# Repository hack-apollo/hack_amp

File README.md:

HACK LABS POWER AMP (TPA3116D2) : https://www.youtube.com/watch?v=O-adCBWkxsg&t=2s                                                                             
Author: HACK实验室                                                                                     
YouTube ID: HACK实验室, welcome to subscribe https://www.youtube.com/c/HACK实验室                                                       
HACK_PowerAmp is a free download and may be used, modified, evaluated and
distributed without charge provided the user adheres to version three of the GNU
General Public License (GPL) and does not remove the copyright notice or this
text.  The GPL V3 text is available on the gnu.org web site
作者：HACK实验室                                                                                        
B站ID：HACK实验室  欢迎订阅 https://space.bilibili.com/395145107                                                                            
微信公众号：HACK实验室，开源资料唯一发布点，定期分享开源硬件以及有价值的技术文章，欢迎关注.

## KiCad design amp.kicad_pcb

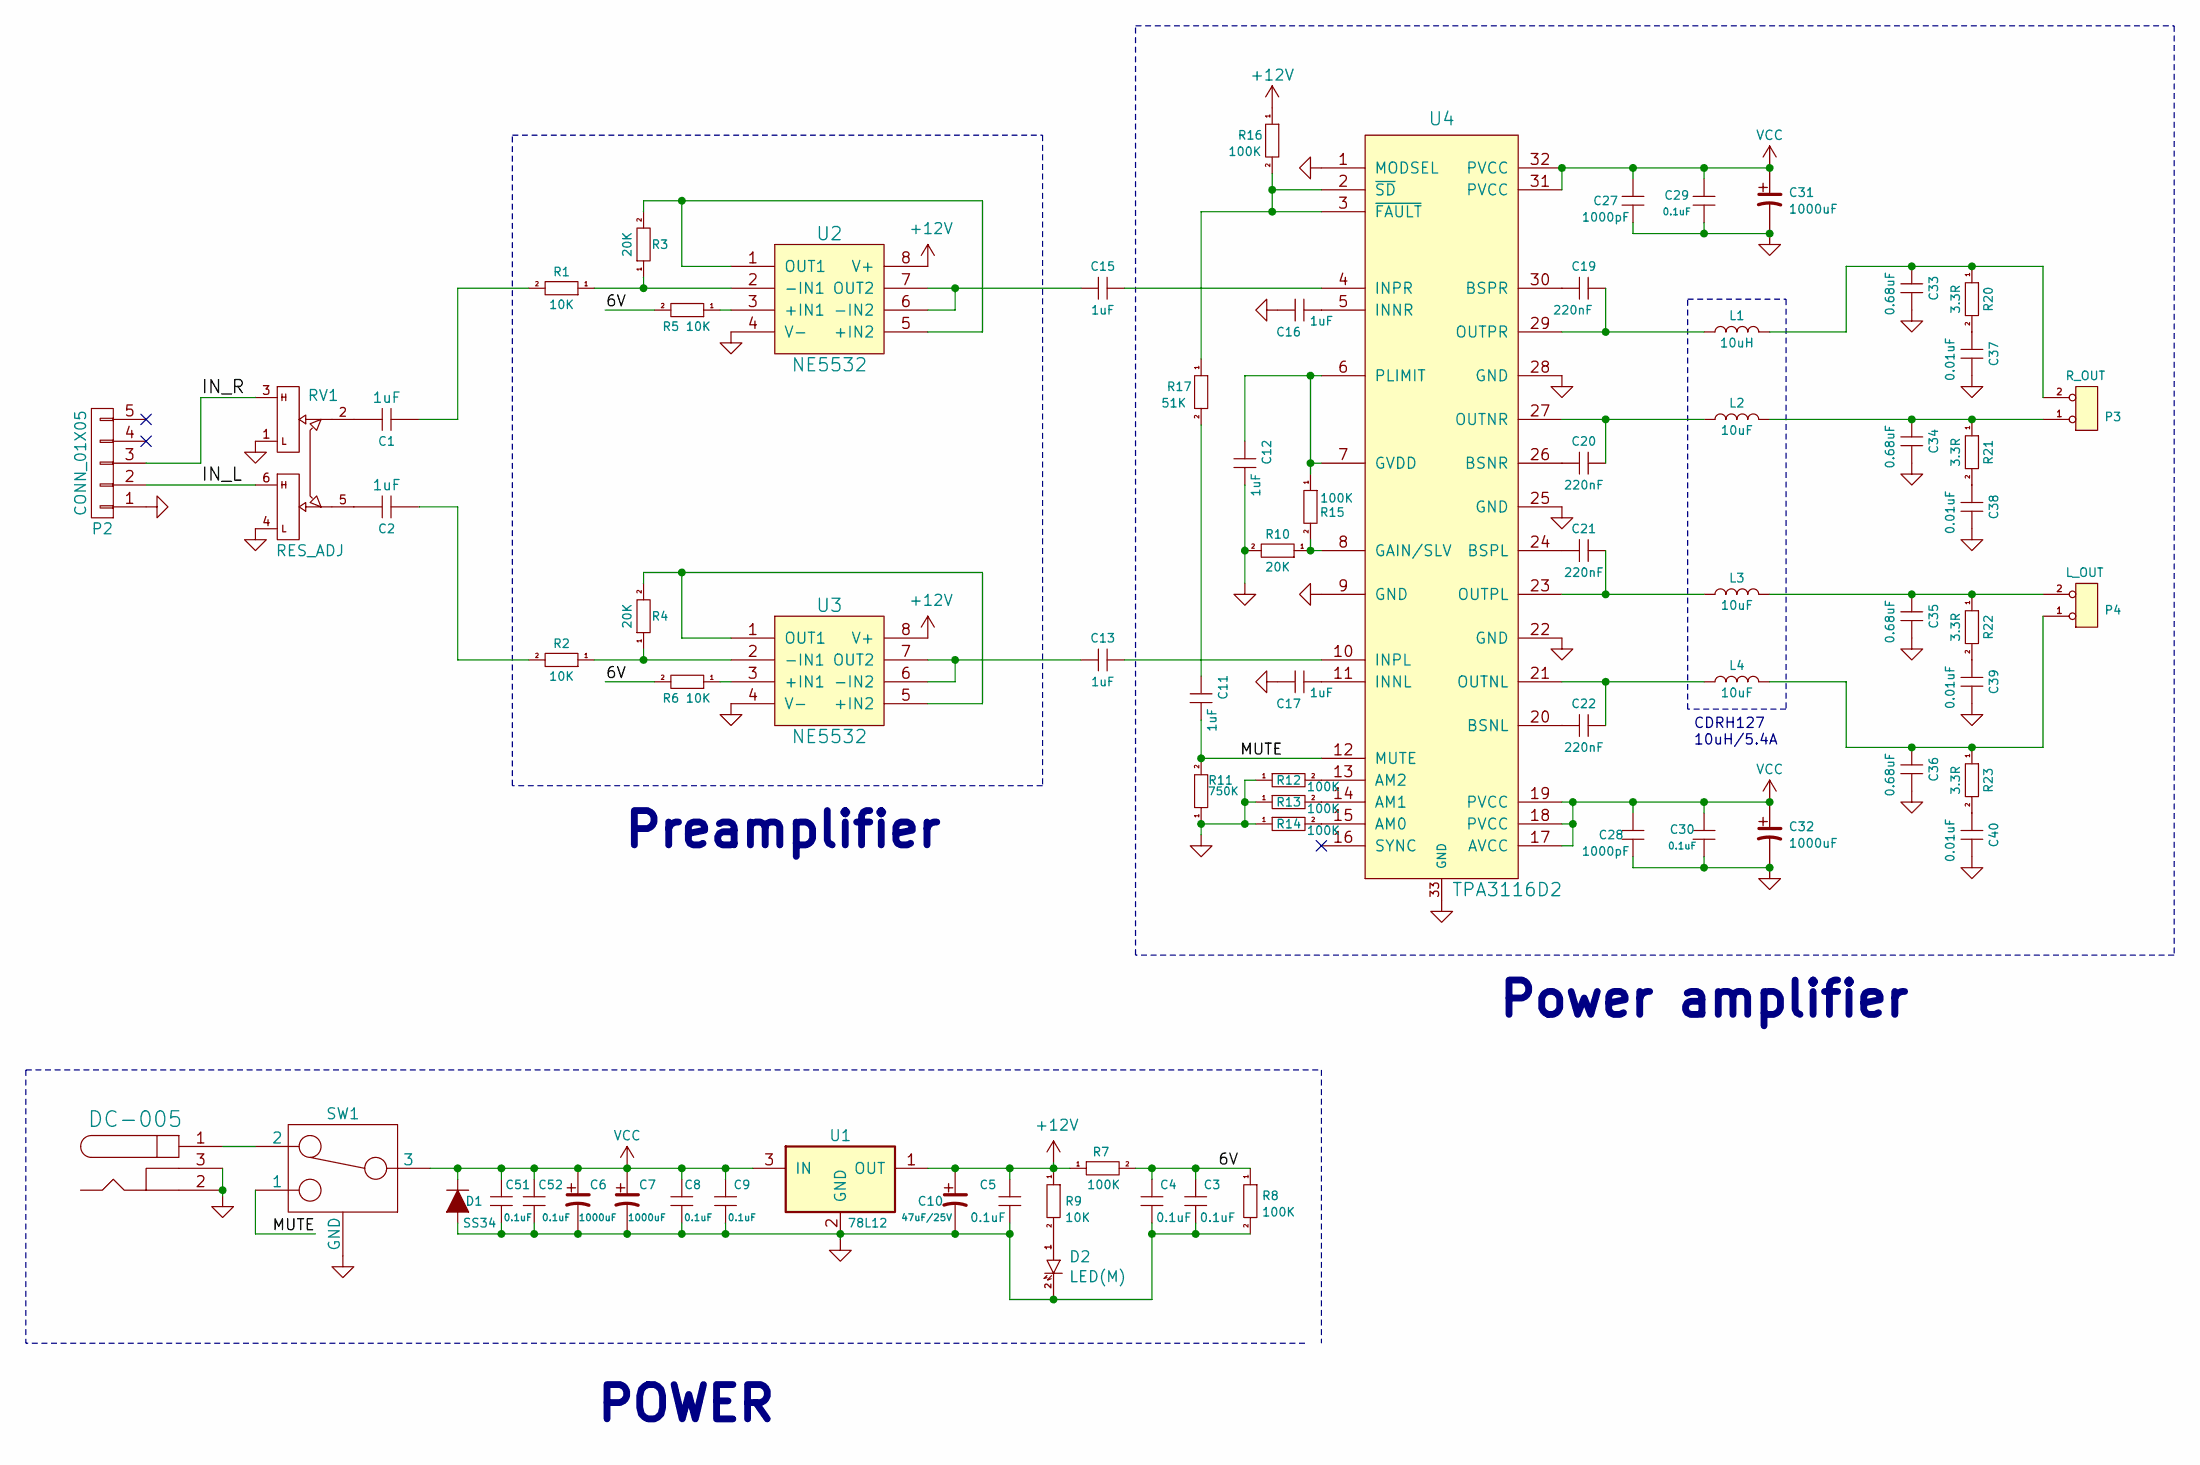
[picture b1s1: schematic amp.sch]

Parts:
C1, C2: 1uF; CP_Radial_D5.0mm_P2.50mm
C3, C4, C5, C8, C9, C29, C30, C51, C52: 0.1uF; 0805_C
C6, C7, C31, C32: 1000uF; CP_Radial_D10.0mm_P5.00mm
C10: 47uF/25V; CP_Radial_D10.0mm_P5.00mm
C11, C12, C13, C15, C16, C17: 1uF; 0805_C
C19, C20, C21, C22: 220nF; 0805_C
C27, C28: 1000pF; 0805_C
C33, C34, C35, C36: 0.68uF; 0805_C
C37, C38, C39, C40: 0.01uF; 0805_C
CON1: DC-005; DCDCJACK_ALIM
D1: SS34; D_SMA
D2: LED(M); LED-3MM
L1: 10uH; L_Bourns_SRR1260
L2, L3, L4: 10uF; L_Bourns_SRR1260
P2: CONN_01X05; Audio_3.5mm
P3: R_OUT; PhoenixContact_MSTBA_2,5_2-G_1x02_P5.00mm_Horizontal
P4: L_OUT; PhoenixContact_MSTBA_2,5_2-G_1x02_P5.00mm_Horizontal
R1, R2, R5, R6, R9: 10K; 0805_R
R3, R4, R10: 20K; 0805_R
R7, R8, R12, R13, R14, R15, R16: 100K; 0805_R
R11: 750K; 0805_R
R17: 51K; 0805_R
R20, R21, R22, R23: 3.3R; 0805_R
RV1: RES_ADJ; ADJ_RES
SW1: SWITCH_INV; SWITCH_Toggle
U1: 78L12; SOT-89-3
U2, U3: NE5532; DIP-8_NEW
U4: TPA3116D2; HTSSOP-32-1EP

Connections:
+9V: C5.1, C10.1, R7.1, R9.1, R16.1, U1.1 (OUT), U2.8 (V+), U3.8 (V+)
/4.5V: C3.1, C4.1, R5.2, R6.2, R7.2, R8.1
/IN_L: P2.2, RV1.6
/IN_R: P2.3, RV1.3
/MUTE: C11.2, R11.2, SW1.1, U4.12 (MUTE)
GND: C3.2, C4.2, C5.2, C6.2, C7.2, C8.2, C9.2, C10.2, C12.2, C16.1, C17.1, C27.2, C28.2, C29.2, C30.2, C31.2, C32.2, C33.1, C34.1, C35.1, C36.1, C37.1, C38.1, C39.1, C40.1, C51.2, C52.2, CON1.2, CON1.3, D1.1 (A), D2.2 (K), P2.1, R8.2, R10.2, R11.1, R12.1, R13.1, R14.1, RV1.1, RV1.4, SW1.0 (GND), U1.2 (GND), U2.4 (V-), U3.4 (V-), U4.1 (MODSEL), U4.9 (GND), U4.22 (GND), U4.25 (GND), U4.28 (GND), U4.33 (GND)
unnamed: C1.1, RV1.2
unnamed: C1.2, R1.2
unnamed: C2.1, RV1.5
unnamed: C2.2, R2.2
unnamed: C11.1, R17.2
unnamed: C12.1, R15.1, U4.6 (PLIMIT), U4.7 (GVDD)
unnamed: C13.1, U3.6 (-IN2), U3.7 (OUT2)
unnamed: C13.2, U4.10 (INPL)
unnamed: C15.1, U2.6 (-IN2), U2.7 (OUT2)
unnamed: C15.2, U4.4 (INPR)
unnamed: C16.2, U4.5 (INNR)
unnamed: C17.2, U4.11 (INNL)
unnamed: C19.1, L1.1, U4.29 (OUTPR)
unnamed: C19.2, U4.30 (BSPR)
unnamed: C20.1, L2.1, U4.27 (OUTNR)
unnamed: C20.2, U4.26 (BSNR)
unnamed: C21.1, L3.1, U4.23 (OUTPL)
unnamed: C21.2, U4.24 (BSPL)
unnamed: C22.1, L4.1, U4.21 (OUTNL)
unnamed: C22.2, U4.20 (BSNL)
unnamed: C33.2, L1.2, P3.2 (PM), R20.1
unnamed: C34.2, L2.2, P3.1, R21.1
unnamed: C35.2, L3.2, P4.2 (PM), R22.1
unnamed: C36.2, L4.2, P4.1, R23.1
unnamed: C37.2, R20.2
unnamed: C38.2, R21.2
unnamed: C39.2, R22.2
unnamed: C40.2, R23.2
unnamed: CON1.1, SW1.2
unnamed: D2.1 (A), R9.2
unnamed: R1.1, R3.1, U2.2 (-IN1)
unnamed: R2.1, R4.1, U3.2 (-IN1)
unnamed: R3.2, U2.1 (OUT1), U2.5 (+IN2)
unnamed: R4.2, U3.1 (OUT1), U3.5 (+IN2)
unnamed: R5.1, U2.3 (+IN1)
unnamed: R6.1, U3.3 (+IN1)
unnamed: R10.1, R15.2, U4.8 (GAIN/SLV)
unnamed: R12.2, U4.13 (AM2)
unnamed: R13.2, U4.14 (AM1)
unnamed: R14.2, U4.15 (AM0)
unnamed: R16.2, R17.1, U4.2 (~SD), U4.3 (~FAULT)
VCC: C6.1, C7.1, C8.1, C9.1, C27.1, C28.1, C29.1, C30.1, C31.1, C32.1, C51.1, C52.1, D1.2 (K), SW1.3, U1.3 (IN), U4.17 (AVCC), U4.18 (PVCC), U4.19 (PVCC), U4.31 (PVCC), U4.32 (PVCC)

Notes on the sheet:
CDRH127 10uH/5.4A
POWER
Preamplifier
Power amplifier

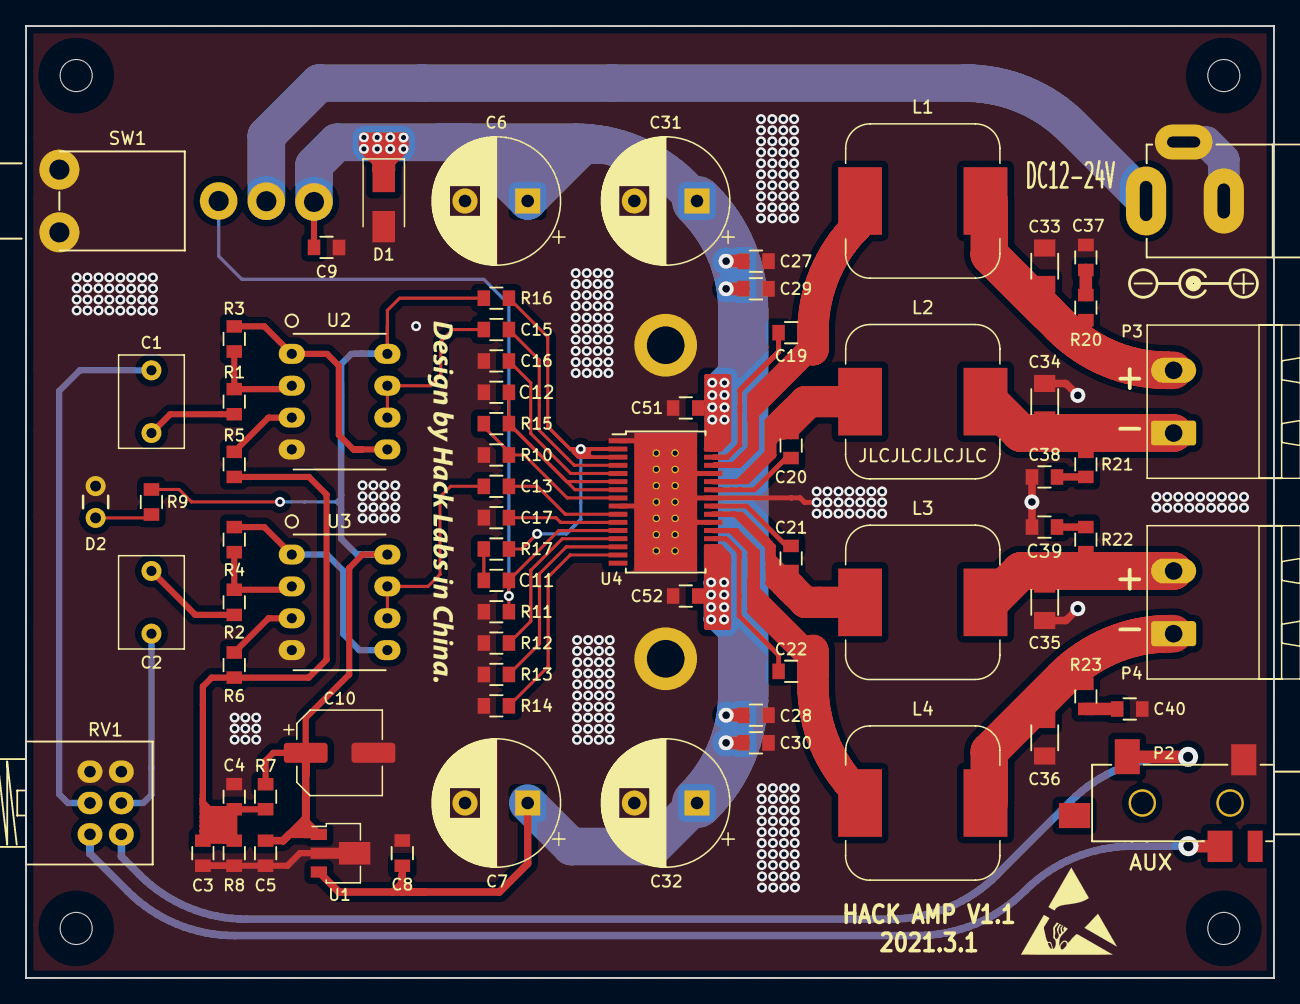
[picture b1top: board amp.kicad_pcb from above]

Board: 2 copper layers, 99.5 x 75.9 mm, 73 parts (0 on the bottom side), 48 nets.

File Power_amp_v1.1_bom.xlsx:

编号 | 名称 | 值 | 封装 | 数量 | 备注
C1,C2 | WIMA MKS 02 | 1uF ±5% 63V | 脚距5mm | 2
C3,C4,C5,C8,C9,C29,C30,C51,C52 | X7R | 0.1uF ±10% 50V | 0805_C | 9
C6,C7,C31,C32 | 伊娜电容 | 220uF 35V（或1000uF/25V） | 10*16mm | 4 | 需注意电源电压要小于耐压值，且需留有余量
C10 | 贴片铝电解电容 | 47UF 25V | 6.3*5.4mm | 1
C11,C12,C13,C15,C16,C17 | X7R | 1uF ±10% 25V | 0805_C | 6
C27,C28 | X7R | 1nF(1000pF) ±5% 50V | 0805_C | 2
C19,C20,C21,C22 | X5R | 220nF ±10% 35V | 0805_C | 4
C33,C34,C35,C36 | X7R | 680nF ±10% 50V | 1206_C | 4
C37,C38,C39,C40 | X7R | 10nF ±10% 100V | 0805_C | 4
R1,R2,R5,R6,R9 |  | 10KΩ | 0805_R | 5
R3,R4,R10 |  | 20KΩ | 0805_R | 3
R7,R8,R12,R13,R14,R15,R16 |  | 100KΩ | 0805_R | 7
R11 |  | 750KΩ | 0805_R | 1
R17 |  | 51KΩ | 0805_R | 1 | 大小决定开机延时时间
R20,R21,R22,R23 |  | 3.3Ω | 0805_R | 4
D1 | 肖特基二极管 | SS34 | SMA | 1
D2 | 直插LED灯 |  | 脚距2.54mm | 1
L1,L2,L3,L4 | 贴片电感 | CDRH127 10uH/5.4A | 12*12*7mm | 4
U1 | CJ78L12 | 0.1A/12V | SOT-89-3 | 1
U2,U3 | NE5532P |  | DIP-8 | 2
U4 | TPA3116D2 |  | TSSOP-32 | 1
SW1 | 钮子开关 | MTS-102C4 |  | 1
RV1 | 09型双联电位器 | B20K |  | 1
CON1 | 电源母座 | DC-005-2.5内芯 |  | 1
P2 | 3.5音频母座 | PJ-328 | 贴片 | 1
P3,P4 | 接线端子 | 2EDG5.08-2P |  | 2
如果整理有误还望见谅，可到“HACK实验室”微信公众号私信通知修改，谢谢！

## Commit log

2021-03-23 first add
2021-03-23 repare bom
2021-03-26 repare bom ——R11
